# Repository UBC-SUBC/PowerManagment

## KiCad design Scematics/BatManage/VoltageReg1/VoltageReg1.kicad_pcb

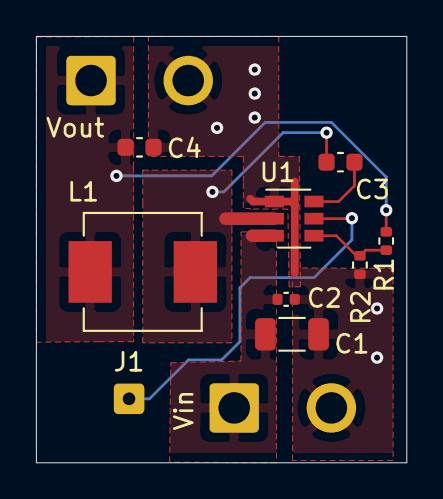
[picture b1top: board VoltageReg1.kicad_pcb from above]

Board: 2 copper layers, 20.6 x 23.7 mm, 11 parts (0 on the bottom side), 7 nets.

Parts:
C1: 10uF; C_1206_3216Metric
C2: 100nF; C_0402_1005Metric
C3: 100nF; C_0603_1608Metric
C4: 22uF; C_0603_1608Metric
J1: Conn_01x01; SolderWire-0.127sqmm_1x01_D0.48mm_OD1mm
L1: 3.3uH; L_Vishay_IHLP-2525
R1: 54.9k; R_0402_1005Metric
R2: 10k; R_0402_1005Metric
U1: TPS565208; SOT-23-6
Vin: 14.8V; SolderWire-1sqmm_1x02_P5.4mm_D1.4mm_OD2.7mm
Vout: 3; SolderWire-1sqmm_1x02_P5.4mm_D1.4mm_OD2.7mm

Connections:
unnamed: C1.1, C2.1, U1.3, Vin.1
unnamed: C1.2, C2.2, C4.2, R2.2, U1.1, Vin.2, Vout.2
unnamed: C3.1, L1.1, U1.2
unnamed: C3.2, U1.6
unnamed: C4.1, L1.2, R1.1, Vout.1
unnamed: J1.1, U1.5
unnamed: R1.2, R2.1, U1.4

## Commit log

2020-11-26 initial upload
2020-11-26 fixed tracked ignored files
2021-02-01 created initial 5V 5A voltage regulator board
2021-02-13 5V 5A schematic following datahseet layout
